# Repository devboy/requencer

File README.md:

# Requencer

A 4-track eurorack step sequencer built around **polymetric randomization** —
each track has independent gate, pitch, velocity and mod subtracks with their
own lengths and clock dividers, and a randomizer that regenerates a whole
track or a single layer at the press of a button. It replaces a live
setup of four sequencers plus utility modules with one hands-on module.

**[▶ Try it live](https://devboy.github.io/requencer/)** — the browser
preview is the real faceplate layout; everything works with mouse or touch.
See the **[manual](docs/manual.md)** for how to play it.

## ⚡ Help wanted: hardware design review

The firmware, engine, and web preview are working and tested — but I'm a
software developer, not a hardware engineer, and this design is about to go
to manufacturing. **I'd be grateful for experienced eyes on the electronics
before I order boards.**

The module is a three-board stack behind a eurorack faceplate:

- **Control board** — buttons, encoders, jacks, LED drivers, shift
  registers, USB-C, SD card, MIDI in.
- **Main board** — RP2350 (PGA2350), DAC8568 CV outputs with op-amp output
  stages (1V/oct), eurorack power entry and regulators.
- Board-to-board via 2×16 shrouded headers.

**Review materials:**

- 📄 **Schematic review PDFs** (one page per subcircuit, net-label style) and
  the full **KiCad projects, gerbers, and STEP files** are attached to the
  latest [GitHub Release](https://github.com/devboy/requencer/releases).
- The design source is [atopile](https://atopile.io/) (`hardware/boards/elec/src/`),
  compiled to KiCad — the PDFs and KiCad files are what you want to look at
  if you don't read `.ato`.

Particularly unsure about: power entry & regulation, the DAC output stage
(1V/oct scaling/offset accuracy), the board-to-board pinout, and the USB-C /
SD / MIDI input circuits. Issues and PRs welcome.

## Features

- 4 tracks × 4 subtracks (gate / pitch / velocity / mod), each with
  independent step length (1–64) and clock divider — polymetric by default.
- Randomizer with per-track scale, root, range, density and velocity config;
  four gate algorithms (RAND / EUCL / SYNC / CLST); 8 factory presets plus
  user presets.
- Drift (per-subtrack stochastic mutation) and per-track transpose with
  scale quantization.
- Free output routing: any subtrack to any of the 4 output jacks.
- Internal, MIDI, or external clock; per-output MIDI channels.

Full documentation: **[docs/manual.md](docs/manual.md)** (also built into
the web app — the MANUAL button).

## Architecture

| Part | What it is |
|------|------------|
| `crates/engine` | `no_std` pure Rust sequencer logic (runs in WASM and on the RP2350) |
| `crates/renderer` | `no_std` display rendering via embedded-graphics |
| `crates/web` | WASM bindings + Canvas2D target for the browser |
| `crates/firmware` | RP2350 firmware: SPI display, DACs, buttons/encoders |
| `web/` | TypeScript preview: Tone.js audio, Web MIDI, canvas faceplate UI |
| `hardware/` | atopile PCB projects (control + main + faceplate) and the build pipeline |

## Development

```bash
make dev      # Vite dev server (builds WASM first)
make test     # All tests: Rust + web + hardware scripts
make rust     # Test + lint + build firmware
make web      # Test + lint + build web bundle
make hardware # Full hardware pipeline (KiCad + FreeRouting required)
```

## License

- Code: [MIT](LICENSE)
- Hardware design (`hardware/`): [CERN-OHL-S v2](hardware/LICENSE) —
  strongly reciprocal open hardware licence.

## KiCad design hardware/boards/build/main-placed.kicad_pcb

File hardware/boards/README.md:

# Requencer Hardware — Design Wiki

Multi-board eurorack sequencer module. Three-board sandwich stack: **faceplate** (front panel PCB) + **control board** (user-facing THT components) + **main board** (MCU, DACs, power).

## System Block Diagram

```
                    FACEPLATE (front panel PCB)
                    ┌─────────────────────────────────────┐
                    │  Display cutout    26× jack holes   │
                    │  36× button holes  2× encoder holes │
                    └──────────────┬──────────────────────┘
                                   │ mechanical mounting
                    CONTROL BOARD (user-facing THT)
                    ┌──────────────┴──────────────────────┐
                    │  FPC connector ──── ST7796 display   │
                    │  36× PB6149L buttons                 │
                    │  2× EC11E encoders                   │
                    │  26× WQP518MA jacks                  │
                    │  2× PJ366ST MIDI jacks               │
                    │  SD card (PJS008U)                    │
                    │  3× IS31FL3216A LED drivers (I2C)    │
                    │  5× 74HC165D shift registers         │
                    │  H11L1S MIDI optocoupler             │
                    └──────────────┬──────────────────────┘
                      2× ShroudedHeader2x16 (64 pins)
                    ┌──────────────┴──────────────────────┐
                    │  PGA2350 MCU (RP2350B, 48 GPIO)     │
                    │  2× DAC80508 (16-bit, 8-ch each)    │
                    │  5× OPA4171A quad op-amps            │
                    │  AMS1117-3.3 LDO                     │
                    │  USB-C (edge-mount)                   │
                    │  Eurorack power header               │
                    └─────────────────────────────────────┘
                    MAIN BOARD (MCU + analog + power)
```

## Documentation Index

### [Parts Catalog](elec/src/components/)

29 active components + [archived parts](elec/src/components/_archive/). Each part has a README with specs, sourcing info, and design rationale.

### Circuit Modules

Design documentation for each circuit block, including component value rationale and signal interfaces.

| Circuit | Board | Description |
|---------|-------|-------------|
| [dac-output](elec/src/circuits/dac-output/) | Main | 2× DAC80508 → 5× OPA4171A → 16 buffered CV/gate outputs |
| [power](elec/src/circuits/power/) | Main | Eurorack ±12V → +5V/+3.3V supply with protection |
| [mcu](elec/src/circuits/mcu/) | Main | PGA2350 (RP2350B) with SPI, I2C, GPIO routing |
| [input-protection](elec/src/circuits/input-protection/) | Main | Voltage divider + Schottky clamp for CV/clock inputs |
| [board-connector](elec/src/circuits/board-connector/) | Both | 2× 2×16 shrouded headers bridging control ↔ main |
| [led-driver](elec/src/circuits/led-driver/) | Control | 3× IS31FL3216A I2C constant-current LED drivers |
| [button-scan](elec/src/circuits/button-scan/) | Control | 5× 74HC165D shift register chain (34 buttons) |
| [midi](elec/src/circuits/midi/) | Control | TRS Type A MIDI IN/OUT (H11L1S optocoupler) |
| [io-jacks](elec/src/circuits/io-jacks/) | Control | 26× WQP518MA mono jacks |
| [display](elec/src/circuits/display/) | Control | ST7796 3.5" SPI TFT (32-pin FPC) — docs only |

### Board Top-Level Modules

| Board | Description |
|-------|-------------|
| [Control](elec/src/boards/control/) | User-facing board: buttons, LEDs, encoders, jacks, display, SD, MIDI |
| [Main](elec/src/boards/main/) | Processing board: MCU, DACs, op-amps, power supply, USB-C |

### Source Structure

See [elec/src/README.md](elec/src/) for the circuit dependency graph and import structure.

## Build System

The hardware pipeline is managed by `Makefile` targets:

| Target | Action |
|--------|--------|
| `make hw-build` | Full pipeline: place → route → ground pours → faceplate → 3D → export |
| `make hw-place` | Component placement + export panel layout |
| `make hw-route` | FreeRouting autorouter |
| `make hw-3d` | 3D model generation + STEP/GLB export |
| `make hw-clean` | Remove build artifacts |

## Layout Source of Truth

KiCad PCB files are the layout authority. The web preview reads from:
- `scripts/placement/export_layout.py` → `web/src/panel-layout.json` (positions from PCB)
- `component-map.json` (UI metadata: dimensions, categories)

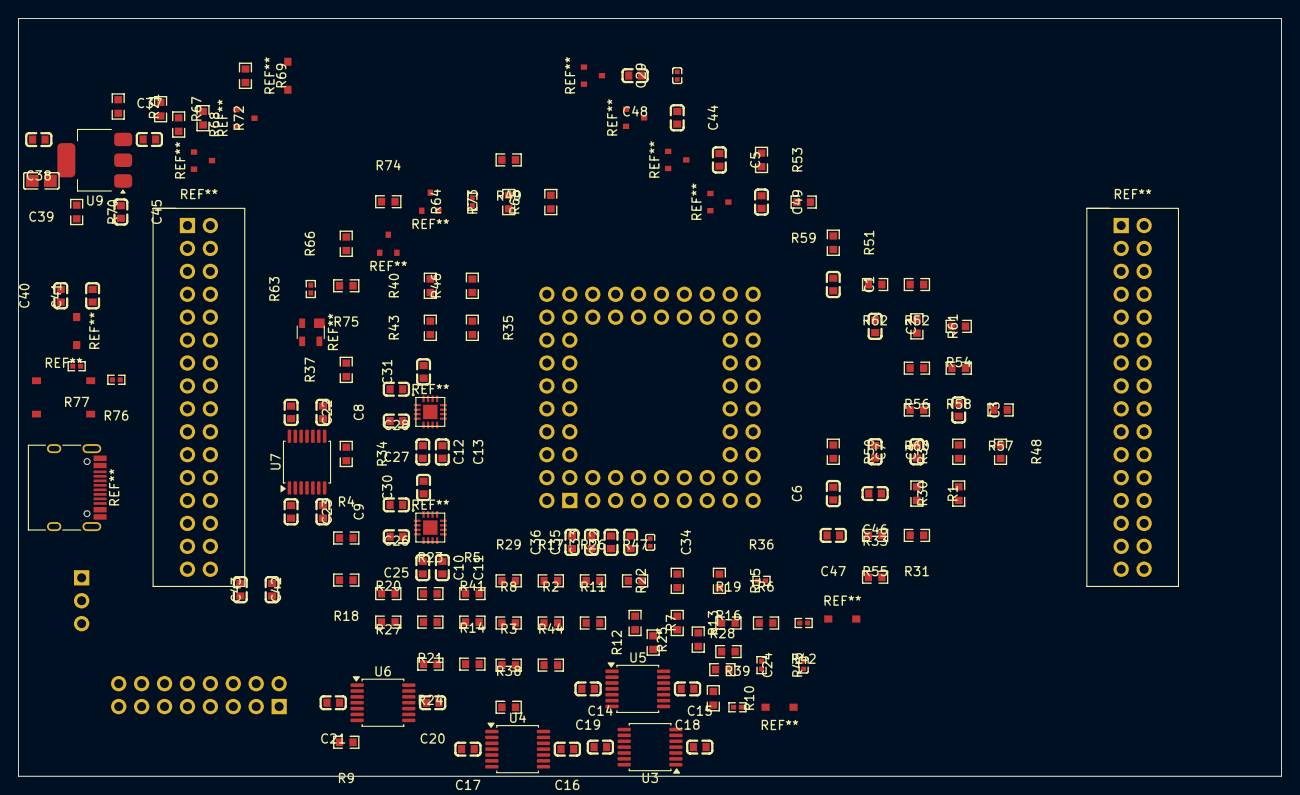
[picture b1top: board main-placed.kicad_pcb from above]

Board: 4 copper layers, 140.0 x 84.0 mm, 132 parts (0 on the bottom side), 61 nets, no tracks yet.

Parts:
C1, C2, C3, C4, C5, C6, C44, C49: 10nF; C0603
C7, C8, C9, C11, C13, C26, C28, C32, C36, C37, C40, C42, C43: 10µF; C0603
C10, C12, C14, C15, C16, C17, C18, C19, C20, C21, C22, C23, C25, C27, C30, C31, C33, C35, C38, C41, C45, C46, C47, C48: 100nF; C0603
C24, C29: 1µF; C0402
C34: 2.2µF; C0402
C39: 47µF; C0805
R1: 10Ω; R0603
R2, R3, R4, R5, R8, R11, R14, R17, R20, R23, R26, R29, R38, R41, R44, R47: 470Ω; R0603
R6, R9, R12, R15, R33: 20kΩ; R0603
R7, R10, R13, R16, R18, R19, R21, R22, R24, R25, R27, R28, R30, R32, R34, R35, R37, R40, R43, R46, R49, R50, R51, R53, R55, R57, R59, R61, R67, R68, R69, R70, R71, R72, R75: 10kΩ; R0603
R31: 15kΩ; R0603
R36, R39, R42, R45: 6.04kΩ; R0402
R48: 200Ω; R0603
R52, R54, R56, R58, R60, R62: 22kΩ; R0603
R63, R64: 5.1kΩ; R0402
R65, R66, R73, R74: 1kΩ; R0603
R76, R77: 27Ω; R0402
U3, U4, U5, U6, U7: TSSOP-14
U9: SOT-223

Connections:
1: R20.1, U4.1
7: R23.1, U4.7
14: R29.1, U4.14
IN1_N: R2.1, U3.1, U3.2
IN2_N: R3.1, U3.6, U3.7
IN3_N: R4.1, U3.8, U3.9
IN4_N: R5.1, U3.13, U3.14
c_3v3_bulk-power-hv: C32.1, C33.1, R48.1, R49.1, R50.1
c_5v_hf-power-hv: C37.1, C40.1, C41.1, R1.1, R66.1, R74.1, U9.3
c_aref-power-hv: C34.1, R48.2
c_dac2_2-power-hv: C7.1, C10.1, C11.1, C12.1, C13.1, R1.2, R31.1, R33.1
c_enc_a_a-power-hv: C1.1, R67.2
c_enc_a_b-power-hv: C2.1, R68.2
c_enc_a_sw-power-hv: C3.1, R69.2
c_enc_b_a-power-hv: C4.1, R70.2
c_enc_b_b-power-hv: C5.1, R71.2
c_enc_b_sw-power-hv: C6.1, R72.2
c_filter-power-hv: C44.1, R51.1, R52.2
c_filter-power-hv-1: C45.1, R53.1, R54.2
c_filter-power-hv-2: C46.1, R55.1, R56.2
c_filter-power-hv-3: C47.1, R57.1, R58.2
c_filter-power-hv-4: C48.1, R59.1, R60.2
c_filter-power-hv-5: C49.1, R61.1, R62.2
c_op5_p-power-hv: C9.1, C15.1, C17.1, C19.1, C21.1, C23.1, C43.1, U3.4, U4.4, U5.4, U6.4, U7.4
c_pitch_ref-power-hv: C24.1, R30.1, R31.2, U7.3
c_ref1_hf-power-hv: C25.1, C26.1
c_ref2_hf-power-hv: C27.1, C28.1
c_ref_filt-power-hv: C29.1, R32.1, R33.2, U7.5
c_vb_hf-power-hv: C35.1, C36.1
c_vio2-power-hv: C30.1, C31.1, C38.1, C39.1, R34.1, R35.1, R67.1, R68.1, R69.1, R70.1, R71.1, R72.1, R75.1, U9.2, U9.4
dac-1: R36.1, R38.1, U5.1
dac-1-1: R6.1, R8.1, U6.1
dac-7: R39.1, R41.1, U5.7
dac-7-1: R9.1, R11.1, U6.7
dac-8: R26.1, U4.8
dac-8-1: R42.1, R44.1, U5.8
dac-8-2: R12.1, R14.1, U6.8
dac-14: R45.1, R47.1, U5.14
dac-14-1: R15.1, R17.1, U6.14
dac-IN1_N: R18.2, R19.1, U4.2
dac-IN1_N-1: R36.2, R37.1, U5.2
dac-IN1_N-2: R6.2, R7.2, U6.2
dac-IN2_N: R21.2, R22.1, U4.6
dac-IN2_N-1: R39.2, R40.1, U5.6
dac-IN2_N-2: R9.2, R10.2, U6.6
dac-IN3_N: R24.2, R25.1, U4.9
dac-IN3_N-1: R42.2, R43.1, U5.9
dac-IN3_N-2: R12.2, R13.2, U6.9
dac-IN4_N: R27.2, R28.1, U4.13
dac-IN4_N-1: R45.2, R46.1, U5.13
dac-IN4_N-2: R15.2, R16.2, U6.13
dac.opamp5-IN3_N: U7.8, U7.9
dac.opamp5-IN4_N: U7.13, U7.14
hv: C1.2, C2.2, C3.2, C4.2, C5.2, C6.2, C7.2, C8.1, C9.2, C10.2, C11.2, C12.2, C13.2, C14.1, C15.2, C16.1, C17.2, C18.1, C19.2, C20.1, C21.2, C22.1, C23.2, C24.2, C25.2, C26.2, C27.2, C28.2, C29.2, C30.2, C31.2, C32.2, C33.2, C34.2, C35.2, C36.2, C37.2, C38.2, C39.2, C40.2, C41.2, C42.1, C43.2, C44.2, C45.2, C46.2, C47.2, C48.2, C49.2, R30.2, R32.2, R37.2, R40.2, R43.2, R46.2, R51.2, R53.2, R55.2, R57.2, R59.2, R61.2, R63.2, R64.2, U7.10, U7.12, U9.1
lv: C8.2, C14.2, C16.2, C18.2, C20.2, C22.2, C42.2, U3.11, U4.11, U5.11, U6.11, U7.11
pitch1: R18.1, R20.2
pitch2: R21.1, R23.2
pitch3: R24.1, R26.2
pitch4: R27.1, R29.2
v_ref_2v: R19.2, R22.2, R25.2, R28.2, U7.1, U7.2
v_ref_mod: U6.3, U6.5, U6.10, U6.12, U7.6, U7.7

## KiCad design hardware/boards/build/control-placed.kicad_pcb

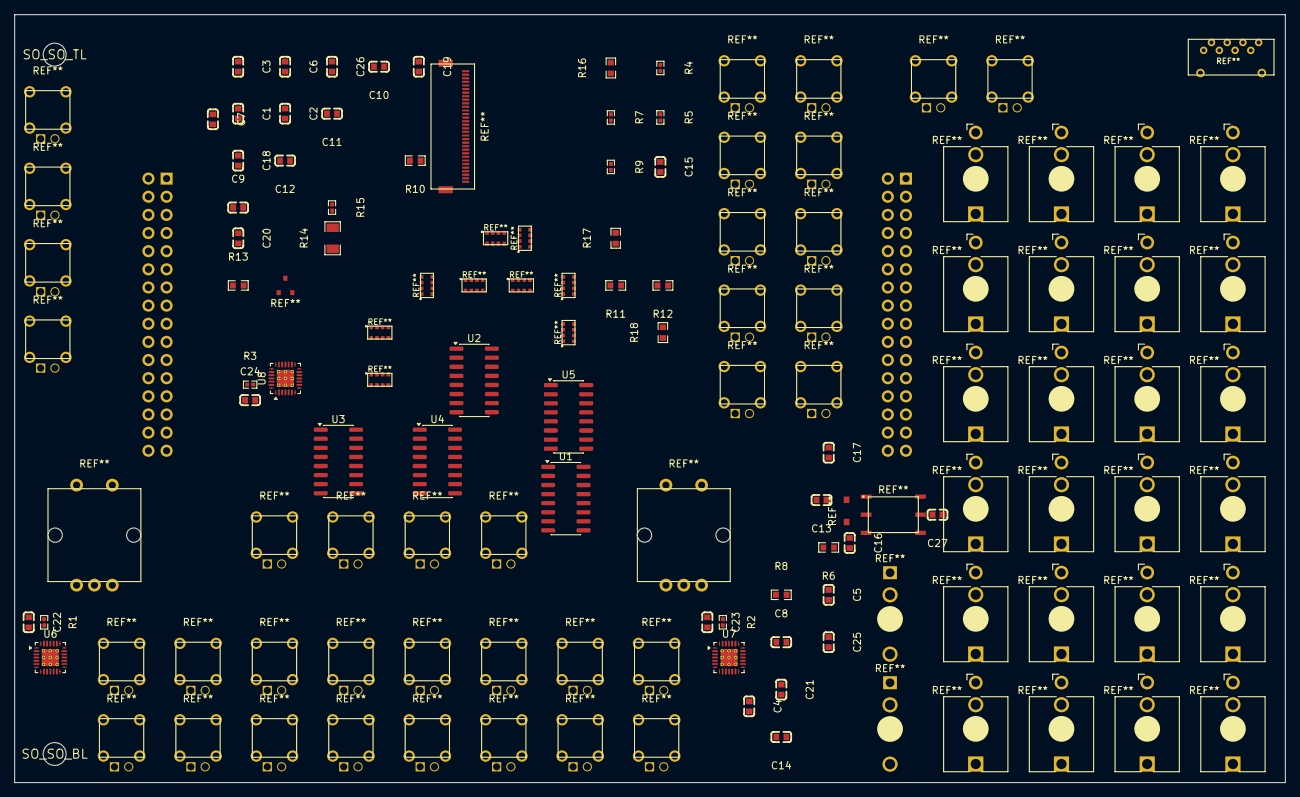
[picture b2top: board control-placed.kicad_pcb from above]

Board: 4 copper layers, 177.9 x 107.5 mm, 55 parts (0 on the bottom side), 19 nets, no tracks yet.

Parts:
C1, C2, C3, C4, C5, C7, C9, C10, C11, C12, C13, C14, C15, C16, C17, C18, C19, C20, C22, C23, C24, C26, C27: 100nF; C0603
C6, C8, C21, C25: 10µF; C0603
R1, R2, R3, R15: 100kΩ; R0402
R4, R5, R9: 4.7kΩ; R0402
R6: 220Ω; R0603
R7: 33Ω; R0402
R8: 10Ω; R0603
R10, R11, R12, R16, R17: 10kΩ; R0603
R13: 100Ω; R0603
R14: 82Ω; R1206
R18: 47kΩ; R0603
SO_SO_BL: M3_Standoff
SO_SO_TL: M3_Standoff
U1, U2, U3, U4, U5: SOIC-16
U6, U7, U8: QFN-28-4x4

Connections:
CLK: U1.2, U2.2, U3.2, U4.2, U5.2
QH: U1.9, U2.10
R_EXT: R1.1, U6.28
SCL: R4.2, U6.23, U7.23, U8.23
SDA: R5.2, U6.24, U7.24, U8.24, U8.25
SH_LD: U1.1, U2.1, U3.1, U4.1, U5.1
buttons-QH: U2.9, U3.10
buttons-QH-1: U3.9, U4.10
buttons-QH-2: U4.9, U5.10
c_filt_a-power-hv: C22.1, U6.27
c_filt_b-power-hv: C23.1, U7.27
c_filt_c-power-hv: C24.1, U8.27
c_lcd_rst-power-hv: C14.1, R16.2
c_sd-power-hv: C1.1, C2.1, C3.1, C4.1, C5.1, C6.1, C7.1, C15.1, C16.1, C17.1, C18.1, C19.1, C20.1, C21.1, R4.1, R5.1, R7.1, R9.1, R10.1, R11.1, R12.1, R16.1, R17.1, R18.1, U1.16, U2.16, U3.16, U4.16, U5.3, U5.4, U5.5, U5.6, U5.16, U6.22, U6.26, U7.22, U7.25, U7.26, U8.22, U8.26
gate: R13.2, R15.1
hv: C8.1, C9.1, C25.1, C26.1, C27.1, R14.1
leds-R_EXT: R2.1, U7.28
leds-R_EXT-1: R3.1, U8.28
lv: C1.2, C2.2, C3.2, C4.2, C5.2, C6.2, C7.2, C8.2, C9.2, C10.2, C11.2, C12.2, C13.2, C14.2, C15.2, C16.2, C17.2, C18.2, C19.2, C20.2, C21.2, C22.2, C23.2, C24.2, C25.2, C26.2, C27.2, R1.2, R2.2, R3.2, R15.2, U1.8, U1.10, U1.15, U2.8, U2.15, U3.8, U3.15, U4.8, U4.15, U5.8, U5.15, U6.1, U6.2, U6.7, U6.16, U6.25, U6.29, U7.1, U7.2, U7.7, U7.16, U7.29, U8.1, U8.2, U8.7, U8.16, U8.29

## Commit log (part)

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2026-03-03 variations v0
2026-03-03 fix: align button columns top and wire VAR button click
    Top-section was using align-items:center, causing misalignment between
    4-button and 5-button columns. FEATURE_IDS was missing 'variation',
    so the 5th feature button (VAR) had no event listeners.
    https://claude.ai/code/session_015mETRcVSDL1agyFQw3YruU
2026-03-03 deploy: 893f951e5b6633c42d8854968a1a2fd5e42a94c9
2026-03-03 Add waveform preview for S+H and slew-random LFO modes
    Replace text placeholders with actual waveform curves:
    - S+H: stepped random values with flat holds between triggers
    - Slew-random: smooth interpolation between random targets
    Both use a seeded RNG so the preview is stable across frames.
    Depth, offset, and width params affect the preview shape.
    https://claude.ai/code/session_016RcBfBFeDNk3mjWSzu6LfJ
2026-03-03 deploy: e43ebc9335e5bfe444ce9e46a584b50adfbb62a0
2026-03-03 deploy: 169c118a9fb88340421e2ccaadd211f00c85080d
2026-03-04 deploy: c32ee80fef2796a49caaafaa393fddc6d75f1331
2026-03-04 Clean up pattern screen: fix bug, extract helper, improve types
    - Fix bug: isSelected ? textDim : textDim → just textDim (identical branches)
    - Extract fillGatePreviewLEDs helper to deduplicate pattern/pattern-load LED code
    - Use row.type discriminant instead of row.paramId for pattern-item checks
    - Make PatternRow a discriminated union so patternIndex is non-optional on
    pattern-item rows, eliminating redundant null guards
    https://claude.ai/code/session_01VS9acswmfw3vcSzbQdSwwn
2026-03-04 deploy: f3ad100217ea00aca70739754fe40447f3a59fe6
2026-03-04 deploy: 8746c481b2d0d2bea3776912126db7be34bb0635
2026-03-04 Fix lint: remove unused import, reduce transformGateValue complexity
    Extract resolveGateOn helper to bring cognitive complexity under threshold.
    Remove unused getEffectiveSimpleStep import from routing.ts.
    https://claude.ai/code/session_01UwcFSnpVJroZMDcYUpz7eg
2026-03-04 deploy: 2dc332f4b31ab117f439bf2acb542c352d5b796b
2026-03-04 deploy: 934cd1ffc2c80195296297e2230cbb657509b524
2026-03-04 deploy: 085624877111c5b89e3cc9e4d2248e4bdac99ce5
2026-03-04 Apply biome formatting fixes
    https://claude.ai/code/session_01LqYohadKK868SEzuQWMBSy
2026-03-04 Remove preview for PR #11
2026-03-04 Remove preview for PR #12
2026-03-05 Fix crash when randomizing tracks with shortened sequence length
    The renderPitchRow function in home.ts accessed steps[i].note for all
    16 display steps without bounds checking. After randomization, the
    steps array is replaced with one matching the (possibly shorter)
    subtrack length, so accessing beyond that length threw an error.
    This crashed the render loop, preventing subsequent tracks from
    drawing (tracks "disappearing") and killing the animation frame
2026-03-05 Remove preview for PR #14
2026-03-05 Fix CI pipeline: remove broken KicadModTree dependency
    - Rewrite generate_footprints.py to output KiCad S-expressions directly
    instead of using KicadModTree (which fails to build on modern setuptools)
    - Remove `pip install KicadModTree` step from CI workflow
    - Use `python3` instead of `python` in workflow commands
    - All scripts now have zero external dependencies (stdlib only)
    - Include generated footprint files and faceplate PCB
2026-03-05 Fix generics dependency: use existing version 4.1.0
    Version 4.4.0 does not exist on the atopile package registry.
    The latest available release of atopile/generics is 4.1.0.
    https://claude.ai/code/session_01HpfsS9xnQqdUmBmR2ys7J5
2026-03-05 fix: replace remaining .p1 → .unnamed[0] for atopile 0.14 stdlib
    The previous sed only caught `.p1 ~` patterns but missed `~ r_*.p1`
    (where .p1 appears at end of expression). Fixed across all 5 files.
    https://claude.ai/code/session_01HpfsS9xnQqdUmBmR2ys7J5
2026-03-05 Remove preview for PR #16
2026-03-05 deploy: 49d9695626a40d83be64a47bfa766fcda82cfd4c
2026-03-05 Add storage options research doc
    Evaluates SPI flash, SD card, FRAM, and USB mass storage for
    preset/pattern persistence. Recommends W25Q128JV (16MB SPI flash)
    as primary storage with optional rear-mounted SD for MIDI import.
    https://claude.ai/code/session_01Vh5xYihAWwSxuCUx1yHCsP
2026-03-05 Complete renderer, web, and firmware crates
    - Renderer: 15 screen modules (home, gate/pitch/vel/mod/mute edit,
    route, rand, mutate, transpose, variation, settings, pattern,
    pattern_load, name_entry) with full render() dispatch
    - Renderer: colors, layout, draw primitives, types (UiState, ScreenMode)
    - Web: Canvas2D framebuffer DrawTarget + wasm-bindgen API with
    step editing, routing, transport, and UI navigation bindings
2026-03-06 deploy: dd4f523d98a0b34ecc3d85c057a6382f86283d50
2026-03-06 Remove preview for PR #20
2026-03-06 Audit fixes: level shifting, reference buffering, MCU pin completion
    - Add 74HCT125 level shifter for DAC SPI (3.3V→5V VIH compliance)
    - Add opamp5 reference buffer quad (2V pitch, 1.667V mod references)
    - Fix pitch CV to non-inverting topology (Vout = 2×Vdac - 2V)
    - Power TLC5947 VCC from 3.3V (fixes SPI level issue, IREF is bandgap-based)
    - Replace mono PJ398SM with stereo PJ301M12 for MIDI TRS Type A
    - Connect SD card detect to GP25
2026-03-06 deploy: 81feed6d767a643391bf2238d45c46289d378e95
2026-03-06 Vertical connectors side by side, centered between steps and jacks
    USB-C and SD card are now portrait (vertical) orientation, laid out
    horizontally next to each other. Positioned as a flex child between
    the main-area and zone-divider, aligned to the bottom — sitting
    nicely in the gap between the step grid and jack zone.
    USB-C: 3.5mm wide × 9mm tall, SD: 2.5mm wide × 12mm tall.
    Total pair width ~8mm — very compact.
2026-03-06 deploy: b47a13381b61aabaa90d7203ca6a30f92ad250b1
2026-03-06 deploy: 199464a98b455c63990628f1b85c6a7fbe979135
2026-03-06 Fix atopile build: add missing footprint/symbol files and fix part references
    - Add local .kicad_mod and .kicad_sym files for parts that were missing them
    (PRTR5V0U2X, 74HCT125D, PGA2350, PJ301M12, MicroSD_Slot, USB_C_Receptacle,
    TactileSwitch)
    - Fix footprint references to include .kicad_mod extension (PRTR5V0U2X, 74HCT125D)
    - Fix PGA2350 supplier_id from unsupported "pimoroni" to "lcsc" placeholder
    - Update generate_footprints.py to write to parts/<PartName>/ directories
2026-03-07 Remove preview for PR #21
2026-03-07 deploy: 456aa47cf20c1b352ae457b0f6dd942b1f529699
2026-03-07 Research: FreeRouting v2.1.0 hang diagnosis and hardware CI/CD best practices
    https://claude.ai/code/session_01FyYq3DgX5o3x9XzTVQ3iR3
2026-03-07 Address firmware production gaps: watchdog, clock pulses, MIDI routing, no-alloc serialization
    - Add RP2350 watchdog timer (8s timeout, fed each main loop iteration)
    - Fix clock output to emit 5ms pulses instead of level toggle (eurorack-compatible)
    - Route MIDI clock messages as tick source when ClockSource::Midi is active
    - Switch postcard serialization from to_allocvec (heap) to to_slice (stack buffer)
    - Remove embedded-alloc dependency and global allocator from firmware
    - Add defmt::warn! error logging on SPI/UART write failures
2026-03-07 Rewrite hardware CI pipeline to fail fast at every stage
    Previous pipeline silently skipped steps when files were missing (using
    if-file-exists guards) and swallowed ERC/DRC errors with || true. This
    meant failures in early stages produced green builds with missing outputs.
    Changes:
    - set -euo pipefail in all docker steps — any command failure stops the build
    - Remove all if-file-exists guards — each stage expects its inputs to exist
2026-03-07 Add CV output processor for eurorack analog outputs
    New cv_output module runs at 4kHz between step boundaries to produce
    continuous DAC values with sub-step timing:
    - Gate length: turns gate off after configurable fraction of step window
    - Ratchets: subdivides gate into 1-4 sub-pulses per step
    - Pitch slide: linear portamento interpolation between notes
    - Mod slew: smooth CV interpolation for modulation changes
2026-03-07 Fix 74HC165D missing footprint, add preflight checks
    - Add is_atomic_part trait, SOIC-16.kicad_mod, and 74HC165D.kicad_sym
    so atopile can place the component on the PCB
    - Fix 74HCT125D LCSC number: C5613 → C5962 (C5613 is the 74HC165D)
    - Add hardware/scripts/preflight_check.py with fast local validation:
    - Atomic part file references (footprint/symbol files exist)
    - Pin count vs footprint pad count
2026-03-07 deploy: f1f2c6a3d281a33075bd0d1fb9405fb8a60dedd0
2026-03-07 ci: run ato sync before build to install dependencies
    https://claude.ai/code/session_01FyYq3DgX5o3x9XzTVQ3iR3
2026-03-08 Optimize SMD placement with netlist-aware ordering
    Replace alphabetical grid placement of SMD components with a
    connectivity-aware algorithm that places electrically-connected
    components adjacent to each other, reducing wire lengths for
    better FreeRouting autoroute results.
    - Add identify_power_nets() to filter GND/VCC/etc from affinity graph
    - Add build_connectivity_graph() using pcbnew pad/net API
2026-03-08 Remove preview for PR #31
2026-03-11 move sd card, usb c, screen back to control board
2026-03-11 Update readme screenshot
2026-03-11 deploy: 74fa3510e83a5210eba40936c88dd87cb67a74f4
2026-03-11 Expand encoder cap section with all knob styles and knurling patterns
    Add detailed dimensions for Davies 1900H, Re'an aluminum, and Rogan PT
    caps. Include LatheGeometry profiles for all three styles. Add procedural
    canvas-based knurling generation (vertical serrations + diamond crosshatch).
    Material reference table covering aluminum, rubber, ABS, and anodized.
    Model-vs-skip decision table for encoder details.
    https://claude.ai/code/session_013eQ3mUFG25Vd8TB2BXhqSe
2026-03-12 deploy: 305db332d598597caa57600f74a553f88db0c30e
2026-03-12 Increase vertical spacing between jack rows by 1mm
    Widen jack row gaps from 12mm to 13mm for better visual separation.
    Clock row stays at y=46, subsequent rows shift down cumulatively:
    CV 58→59, gate 70→72, pitch 82→85, vel 94→98, mod 106→111.
    https://claude.ai/code/session_01AotRtu6SAxvsieLt75dex9
2026-03-13 Gitignore __pycache__, build stamps, and log files
2026-03-14 Single sided SMD assebly
2026-03-14 Remove preview for PR #41
2026-03-18 deploy: fd080133b7c09fb5e7044da727af534753dd10bf
2026-03-18 Fix visuals
